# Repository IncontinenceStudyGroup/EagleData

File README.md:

# EagleData

Mits design pro で基板外径などのラインを作成するときは右上の`アプリケーション`ボタンから`Converter`モードにしてからおこなう．

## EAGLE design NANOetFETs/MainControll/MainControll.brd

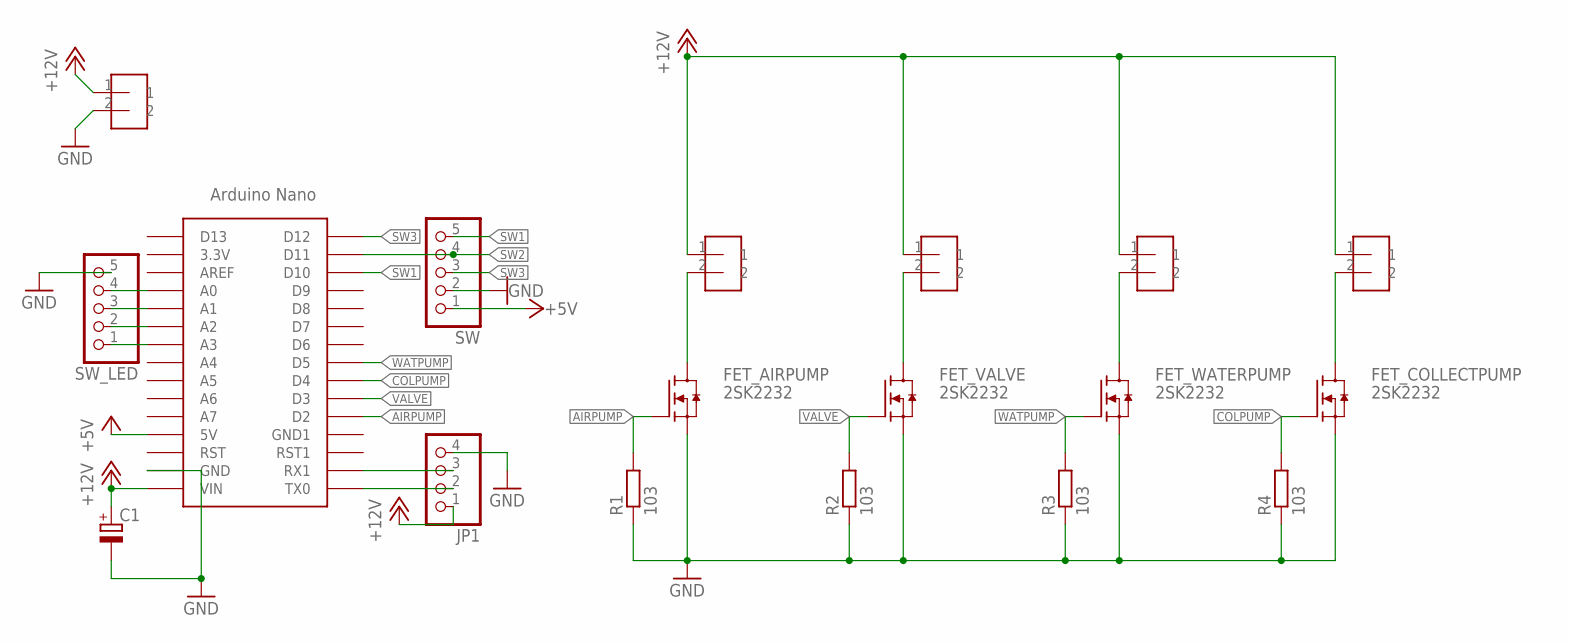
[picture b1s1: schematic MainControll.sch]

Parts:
C1: CPOL-EUE2.5-5; E2,5-5
FET_AIRPUMP: 2SK2232; TO220
FET_COLLECTPUMP: 2SK2232; TO220
FET_VALVE: 2SK2232; TO220
FET_WATERPUMP: 2SK2232; TO220
JP1: PINHD-1X4; 1X04
R1, R2, R3, R4: 103; 0204/5
SW: PINHD-1X5; 1X05
SW_LED: PINHD-1X5; 1X05
TERMINAL_AIRPUMP: TERMINAL_BLOCK_5.08MM; TERMINAL_BLOCK_5.8MM
TERMINAL_COLLECTPUMP: TERMINAL_BLOCK_5.08MM; TERMINAL_BLOCK_5.8MM
TERMINAL_VALVE: TERMINAL_BLOCK_5.08MM; TERMINAL_BLOCK_5.8MM
TERMINAL_WATERPUMP: TERMINAL_BLOCK_5.08MM; TERMINAL_BLOCK_5.8MM
U$1: TERMINAL_BLOCK_5.08MM; TERMINAL_BLOCK_5.8MM
U$2: NANO_DIL_RECEPTOR; NANO_DIL

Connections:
+5V: SW.1, U$2.5V
+12V: C1.+, JP1.1, TERMINAL_AIRPUMP.1, TERMINAL_COLLECTPUMP.1, TERMINAL_VALVE.1, TERMINAL_WATERPUMP.1, U$1.1, U$2.VIN
AIRPUMP: FET_AIRPUMP.1 (G), R1.2, U$2.D2
COLPUMP: FET_COLLECTPUMP.1 (G), R4.2, U$2.D4
GND: C1.-, FET_AIRPUMP.3 (S), FET_COLLECTPUMP.3 (S), FET_VALVE.3 (S), FET_WATERPUMP.3 (S), JP1.4, R1.1, R2.1, R3.1, R4.1, SW.2, SW_LED.5, U$1.2, U$2.GND
unnamed: JP1.3, U$2.RX1
unnamed: JP1.2, U$2.TX0
unnamed: FET_AIRPUMP.2 (D), TERMINAL_AIRPUMP.2
unnamed: FET_VALVE.2 (D), TERMINAL_VALVE.2
unnamed: FET_WATERPUMP.2 (D), TERMINAL_WATERPUMP.2
unnamed: FET_COLLECTPUMP.2 (D), TERMINAL_COLLECTPUMP.2
unnamed: SW_LED.4, U$2.A0
unnamed: SW_LED.3, U$2.A1
unnamed: SW_LED.2, U$2.A2
unnamed: SW_LED.1, U$2.A3
SW1: SW.5, U$2.D10
SW2: SW.4, U$2.D11
SW3: SW.3, U$2.D12
VALVE: FET_VALVE.1 (G), R2.2, U$2.D3
WATPUMP: FET_WATERPUMP.1 (G), R3.2, U$2.D5

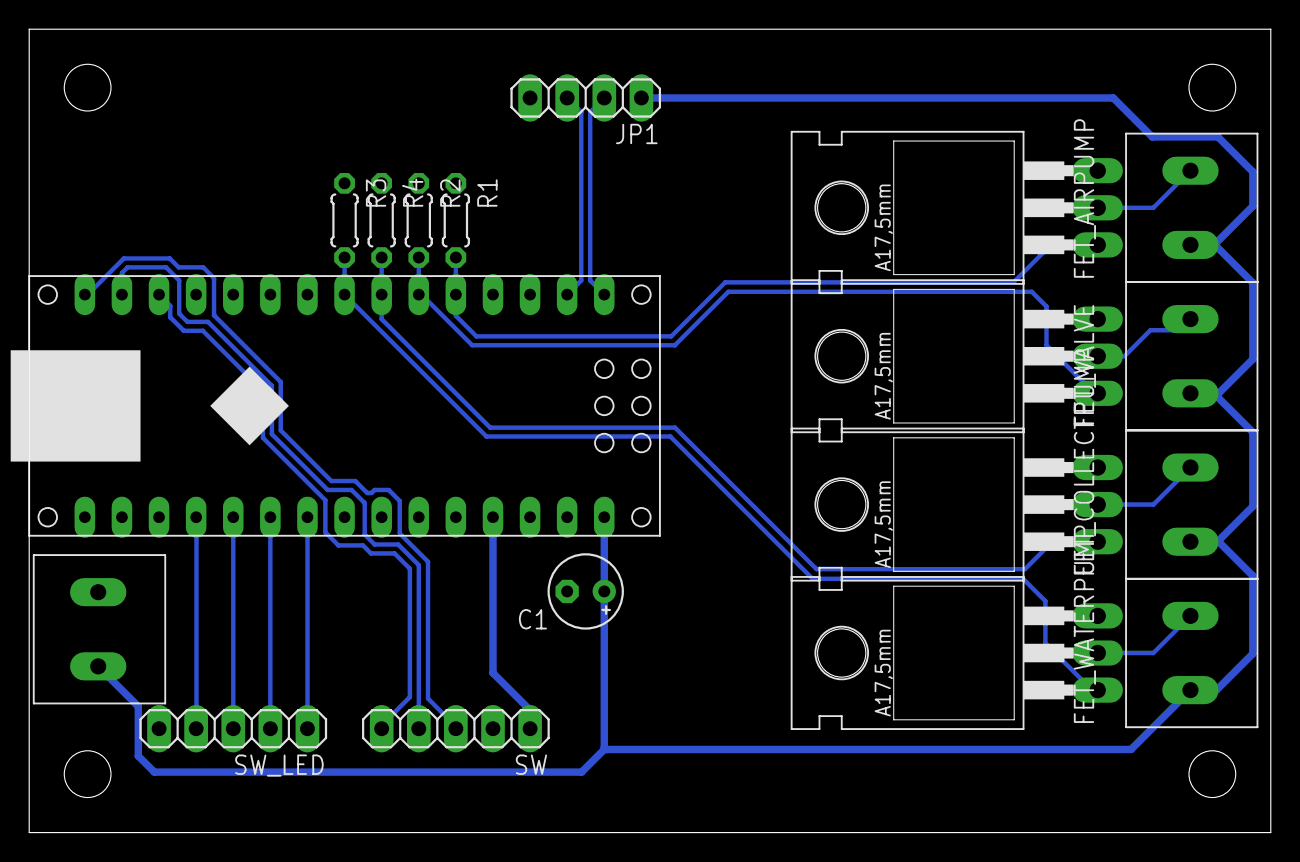
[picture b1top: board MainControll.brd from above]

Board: 2 copper layers, 85.0 x 55.0 mm, 18 parts (0 on the bottom side), 20 nets.

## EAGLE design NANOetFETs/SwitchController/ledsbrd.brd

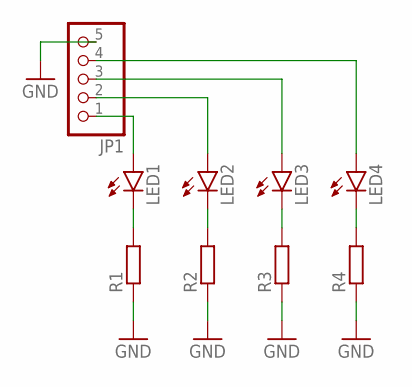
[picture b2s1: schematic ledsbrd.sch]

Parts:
JP1: PINHD-1X5; 1X05
LED1, LED2, LED3, LED4: LED5MM
R1, R2, R3, R4: R-EU_0204/5; 0204/5

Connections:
GND: JP1.5, R1.1, R2.1, R3.1, R4.1
unnamed: LED1.K (C), R1.2
unnamed: LED2.K (C), R2.2
unnamed: LED3.K (C), R3.2
unnamed: LED4.K (C), R4.2
unnamed: JP1.1, LED1.A
unnamed: JP1.2, LED2.A
unnamed: JP1.3, LED3.A
unnamed: JP1.4, LED4.A

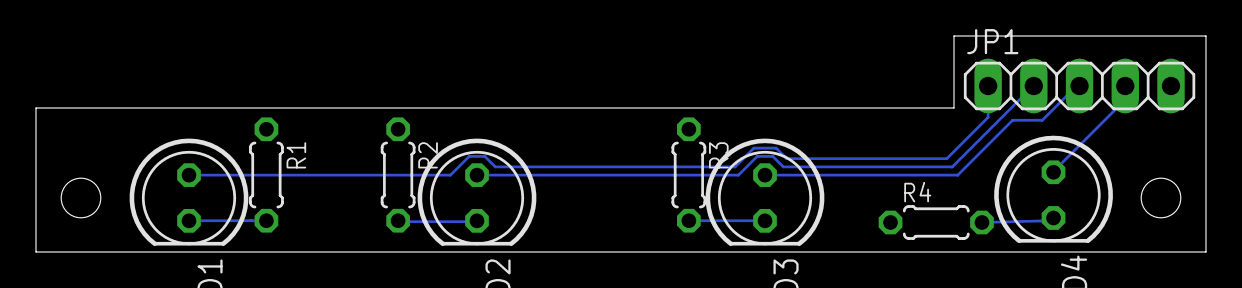
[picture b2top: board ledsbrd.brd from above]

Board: 2 copper layers, 65.0 x 12.0 mm, 9 parts (0 on the bottom side), 9 nets.

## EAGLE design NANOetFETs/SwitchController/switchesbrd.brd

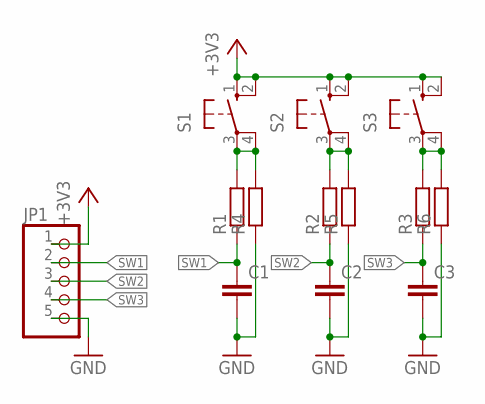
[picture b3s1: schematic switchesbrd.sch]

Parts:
C1, C2, C3: C-EU025-025X050; C025-025X050
JP1: PINHD-1X5; 1X05
R1, R2, R3, R4, R5, R6: R-EU_0204/5; 0204/5
S1, S2, S3: 10-XX; B3F-10XX

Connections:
+3V3: JP1.1, S1.1 (S), S1.2 (S1), S2.1 (S), S2.2 (S1), S3.1 (S), S3.2 (S1)
GND: C1.2, C2.2, C3.2, JP1.5, R4.1, R5.1, R6.1
unnamed: R1.2, R4.2, S1.3, S1.4 (P1)
unnamed: R2.2, R5.2, S2.3, S2.4 (P1)
unnamed: R3.2, R6.2, S3.3, S3.4 (P1)
SW1: C1.1, JP1.2, R1.1
SW2: C2.1, JP1.3, R2.1
SW3: C3.1, JP1.4, R3.1

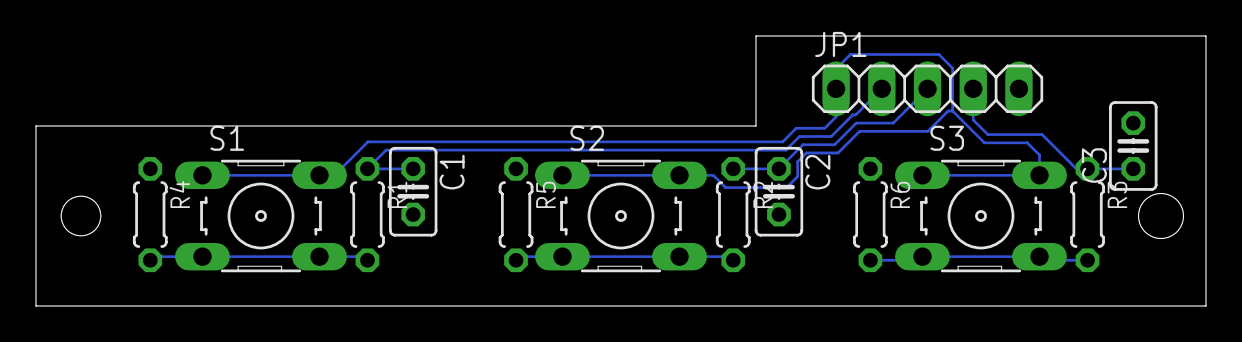
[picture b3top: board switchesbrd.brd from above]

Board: 2 copper layers, 65.0 x 15.0 mm, 13 parts (0 on the bottom side), 8 nets.

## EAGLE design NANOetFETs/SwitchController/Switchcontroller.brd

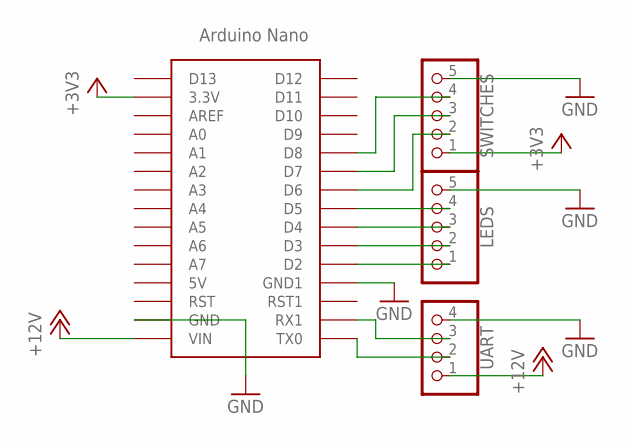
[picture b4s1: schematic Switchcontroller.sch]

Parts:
LEDS: PINHD-1X5; 1X05
SWITCHES: PINHD-1X5; 1X05
U$1: NANO_DIL_RECEPTORPIN-M1; NANO_DIL_M1
UART: PINHD-1X4; 1X04

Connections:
+3V3: SWITCHES.1, U$1.3.3V
+12V: U$1.VIN, UART.1
GND: LEDS.5, SWITCHES.5, U$1.GND, U$1.GND1, UART.4
unnamed: U$1.TX0, UART.2
unnamed: U$1.RX1, UART.3
unnamed: LEDS.3, U$1.D4
unnamed: LEDS.2, U$1.D3
unnamed: LEDS.1, U$1.D2
unnamed: LEDS.4, U$1.D5
unnamed: SWITCHES.2, U$1.D6
unnamed: SWITCHES.3, U$1.D7
unnamed: SWITCHES.4, U$1.D8

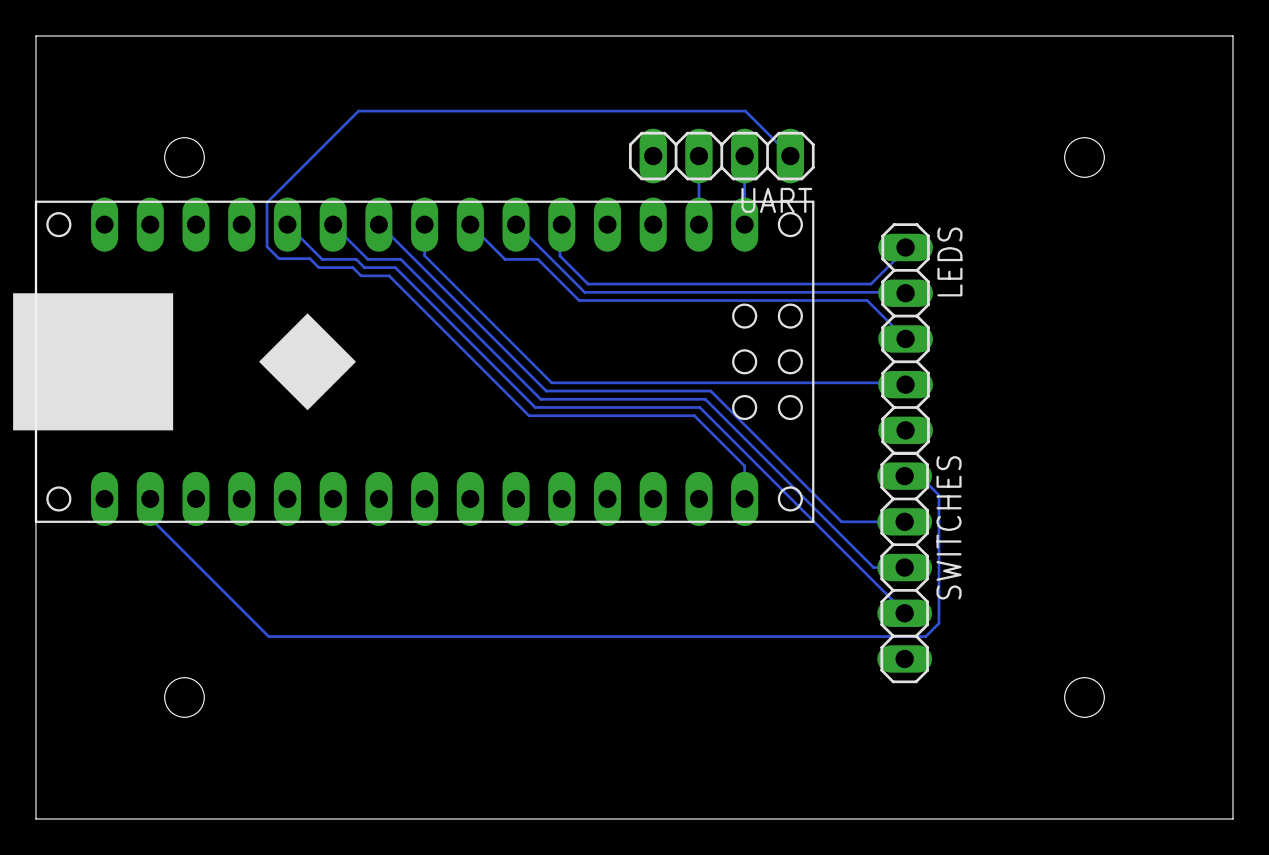
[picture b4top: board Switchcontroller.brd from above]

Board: 2 copper layers, 66.5 x 43.5 mm, 4 parts (0 on the bottom side), 12 nets.

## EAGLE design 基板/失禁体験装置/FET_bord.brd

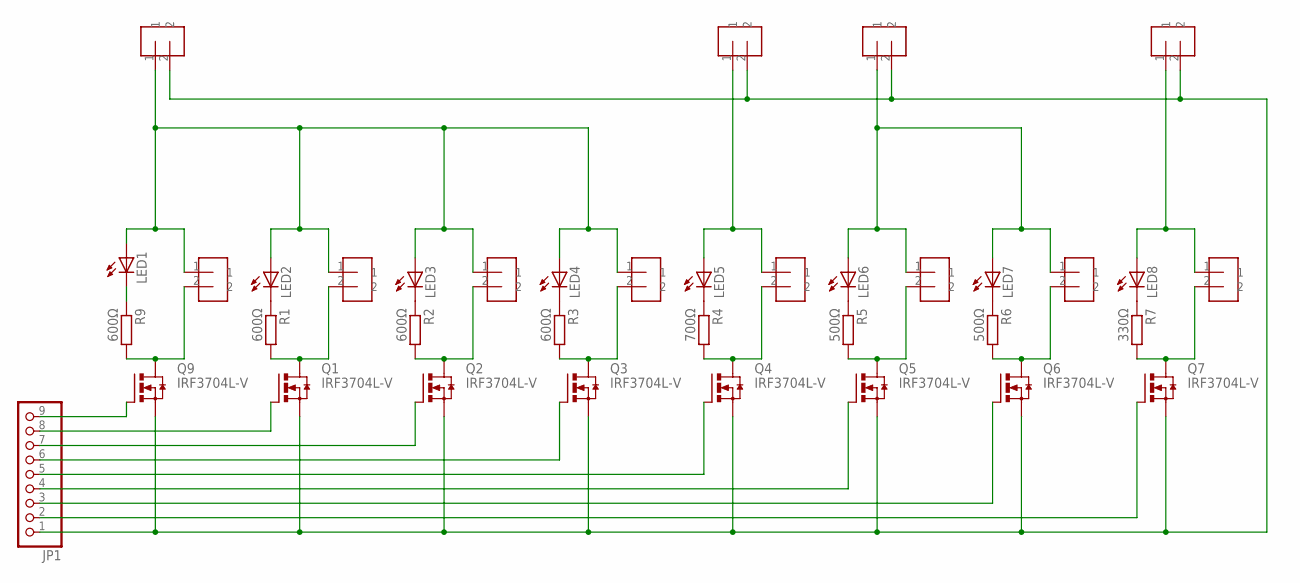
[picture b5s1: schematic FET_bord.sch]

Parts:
3.3V, 5V, 7V, 12V: TERMINAL_BLOCK_5.08MM; TERMINAL_BLOCK_5.8MM
JP1: PINHD-1X9; 1X09
LED1, LED2, LED3, LED4, LED5, LED6, LED7, LED8: LED3MM
Q1, Q2, Q3, Q4, Q5, Q6, Q7, Q9: IRF3704L-V; TO262-V
R1, R2, R3, R9: 600Ω; 0207/15
R4: 700Ω; 0207/15
R5, R6: 500Ω; 0207/15
R7: 330Ω; 0207/15
U$1, U$2, U$3, U$4, U$5, U$6, U$7, U$8: TERMINAL_BLOCK_5.08MM; TERMINAL_BLOCK_5.8MM

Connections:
unnamed: LED2.K (C), R1.1
unnamed: 12V.1, LED1.A, LED2.A, LED3.A, LED4.A, U$1.1, U$2.1, U$3.1, U$4.1
unnamed: Q1.2 (D), R1.2, U$2.2
unnamed: LED3.K (C), R2.1
unnamed: LED4.K (C), R3.1
unnamed: Q2.2 (D), R2.2, U$3.2
unnamed: LED5.K (C), R4.1
unnamed: LED8.K (C), R7.1
unnamed: LED1.K (C), R9.1
unnamed: LED7.K (C), R6.1
unnamed: Q9.2 (D), R9.2, U$1.2
unnamed: Q3.2 (D), R3.2, U$4.2
unnamed: LED6.K (C), R5.1
unnamed: 7V.1, LED5.A, U$5.1
unnamed: Q4.2 (D), R4.2, U$5.2
unnamed: Q5.2 (D), R5.2, U$6.2
unnamed: 5V.1, LED6.A, LED7.A, U$6.1, U$7.1
unnamed: Q6.2 (D), R6.2, U$7.2
unnamed: 3.3V.1, LED8.A, U$8.1
unnamed: Q7.2 (D), R7.2, U$8.2
unnamed: JP1.9, Q9.1 (G)
unnamed: JP1.8, Q1.1 (G)
unnamed: JP1.7, Q2.1 (G)
unnamed: JP1.6, Q3.1 (G)
unnamed: JP1.5, Q4.1 (G)
unnamed: JP1.4, Q5.1 (G)
unnamed: JP1.3, Q6.1 (G)
unnamed: JP1.2, Q7.1 (G)
unnamed: 3.3V.2, 5V.2, 7V.2, 12V.2, JP1.1, Q1.3 (S), Q2.3 (S), Q3.3 (S), Q4.3 (S), Q5.3 (S), Q6.3 (S), Q7.3 (S), Q9.3 (S)

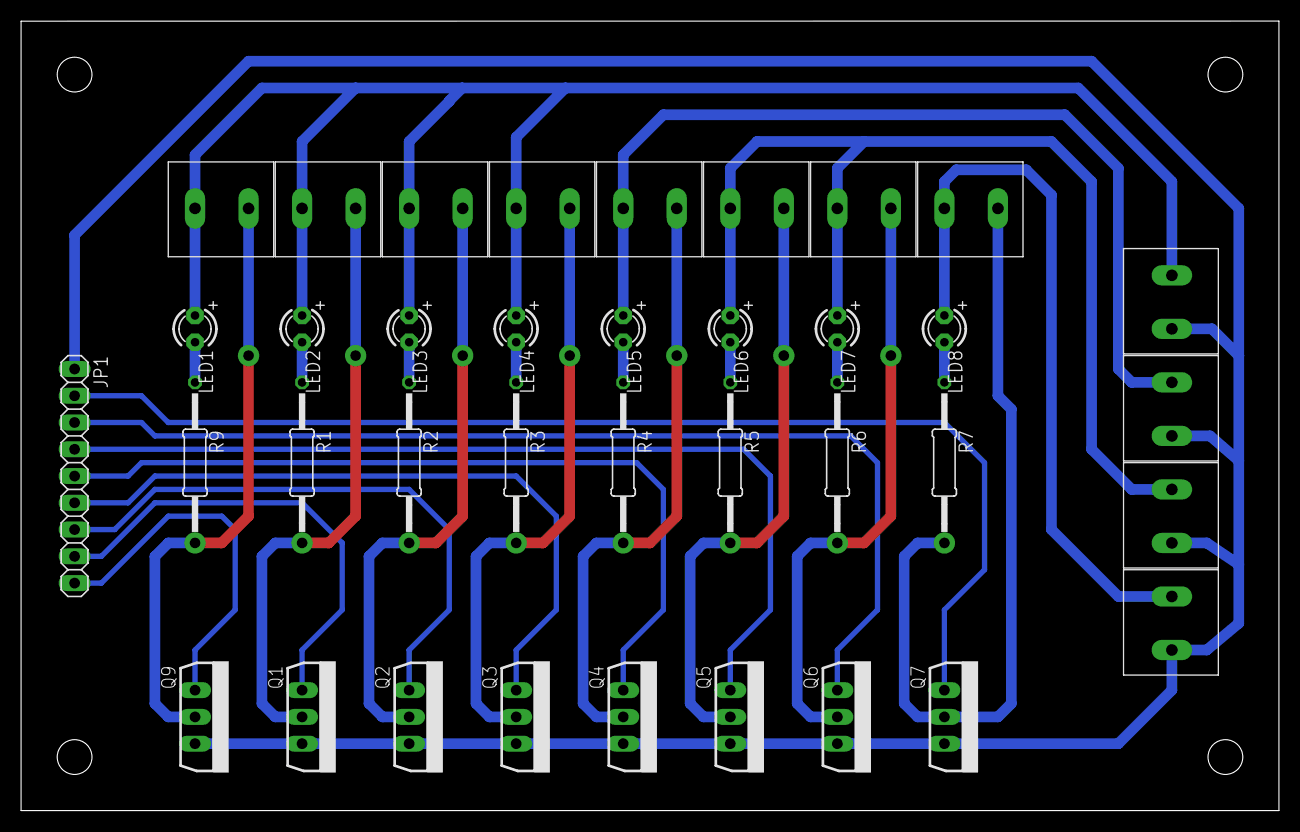
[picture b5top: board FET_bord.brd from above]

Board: 2 copper layers, 119.4 x 74.9 mm, 37 parts (0 on the bottom side), 29 nets.

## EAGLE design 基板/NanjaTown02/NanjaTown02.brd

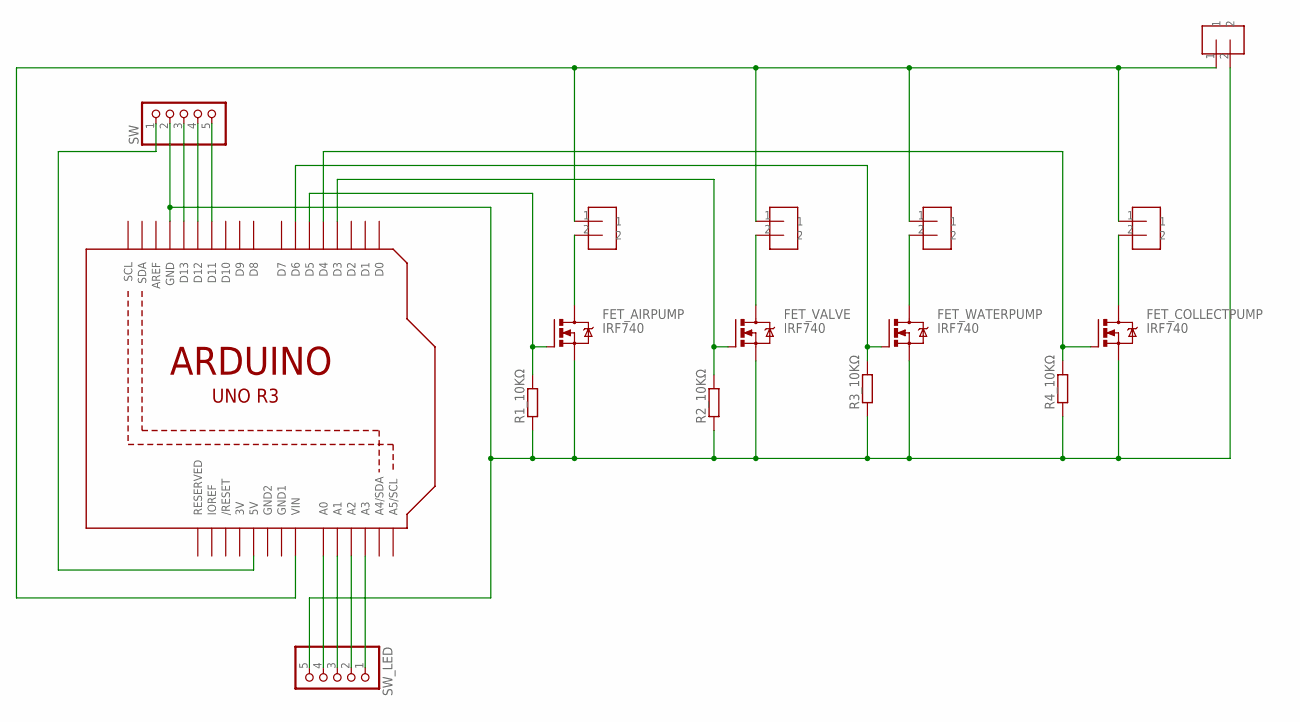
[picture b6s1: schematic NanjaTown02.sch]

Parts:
FET_AIRPUMP: IRF740; TO220BV
FET_COLLECTPUMP: IRF740; TO220BV
FET_VALVE: IRF740; TO220BV
FET_WATERPUMP: IRF740; TO220BV
R1_10KΩ, R2_10KΩ, R3_10KΩ, R4_10KΩ: R-EU_0207/10; 0207/10
SW: PINHD-1X5; 1X05
SW_LED: PINHD-1X5/90; 1X05/90
TERMINAL_AIRPUMP: TERMINAL_BLOCK_5.08MM; TERMINAL_BLOCK_5.8MM
TERMINAL_COLLECTPUMP: TERMINAL_BLOCK_5.08MM; TERMINAL_BLOCK_5.8MM
TERMINAL_VALVE: TERMINAL_BLOCK_5.08MM; TERMINAL_BLOCK_5.8MM
TERMINAL_WATERPUMP: TERMINAL_BLOCK_5.08MM; TERMINAL_BLOCK_5.8MM
U1: ARDUINOR3-DIMENSION; ARDUINOR3
U$1: TERMINAL_BLOCK_5.08MM; TERMINAL_BLOCK_5.8MM

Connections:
3V: U1.3V
GND1: U1.GND1
GND2: U1.GND2
unnamed: FET_AIRPUMP.G, R1_10KΩ.2, U1.D5
unnamed: FET_VALVE.G, R2_10KΩ.2, U1.D3
unnamed: FET_WATERPUMP.G, R3_10KΩ.2, U1.D6
unnamed: FET_COLLECTPUMP.G, R4_10KΩ.2, U1.D4
unnamed: TERMINAL_AIRPUMP.1, TERMINAL_COLLECTPUMP.1, TERMINAL_VALVE.1, TERMINAL_WATERPUMP.1, U1.VIN, U$1.1
unnamed: FET_AIRPUMP.D, TERMINAL_AIRPUMP.2
unnamed: FET_VALVE.D, TERMINAL_VALVE.2
unnamed: FET_WATERPUMP.D, TERMINAL_WATERPUMP.2
unnamed: FET_COLLECTPUMP.D, TERMINAL_COLLECTPUMP.2
unnamed: SW_LED.4, U1.A0
unnamed: SW_LED.3, U1.A1
unnamed: SW_LED.2, U1.A2
unnamed: SW_LED.1, U1.A3
unnamed: FET_AIRPUMP.S, FET_COLLECTPUMP.S, FET_VALVE.S, FET_WATERPUMP.S, R1_10KΩ.1, R2_10KΩ.1, R3_10KΩ.1, R4_10KΩ.1, SW.2, SW_LED.5, U1.GND, U$1.2
unnamed: SW.5, U1.D11
unnamed: SW.4, U1.D12
unnamed: SW.3, U1.D13
unnamed: SW.1, U1.5V

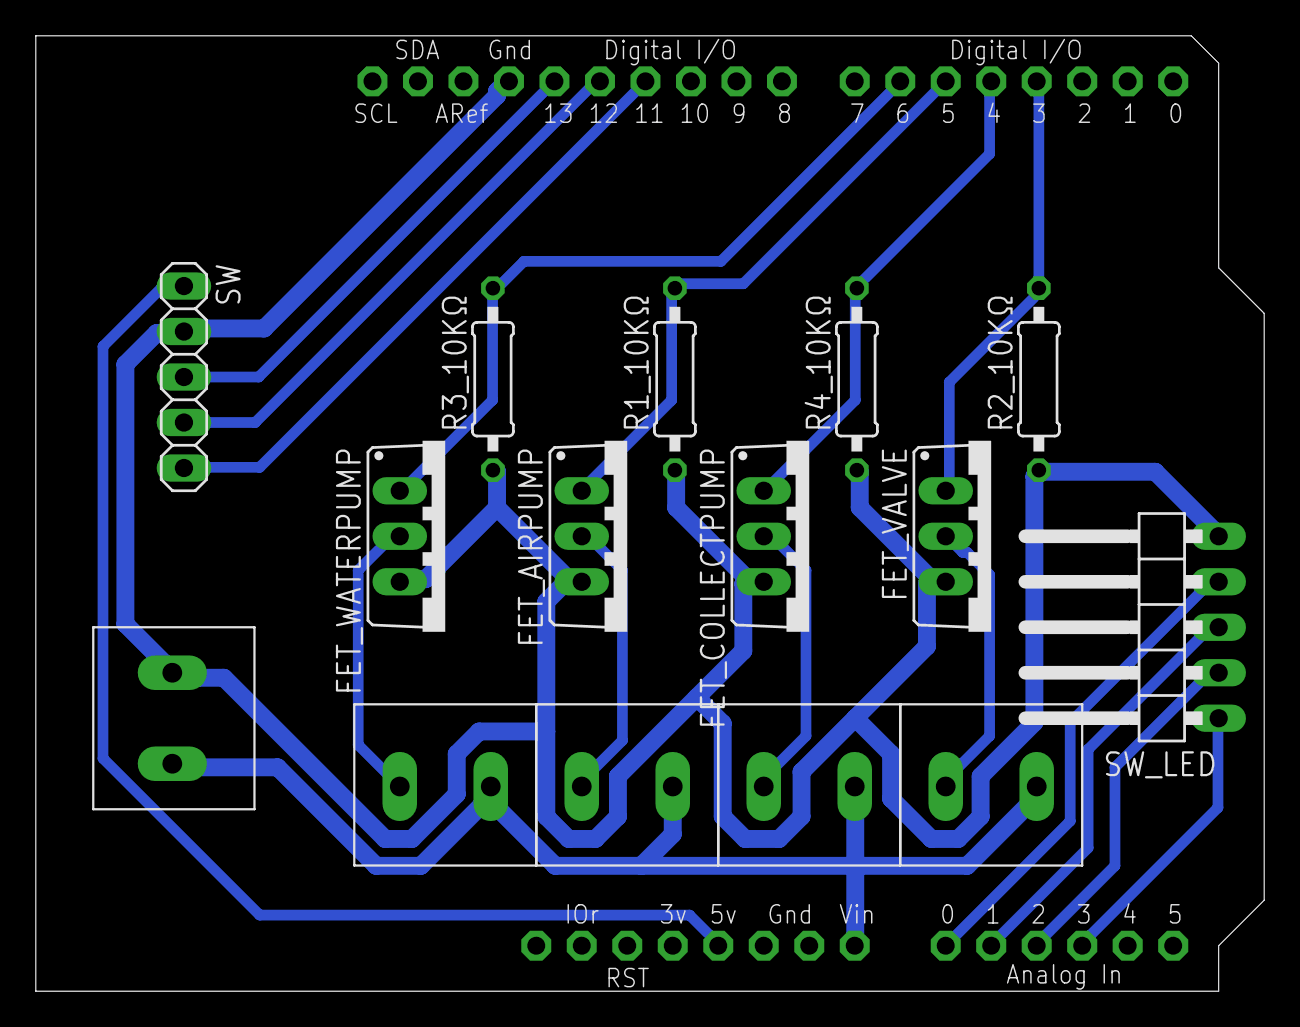
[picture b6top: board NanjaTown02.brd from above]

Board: 2 copper layers, 68.6 x 53.3 mm, 16 parts (0 on the bottom side), 18 nets.

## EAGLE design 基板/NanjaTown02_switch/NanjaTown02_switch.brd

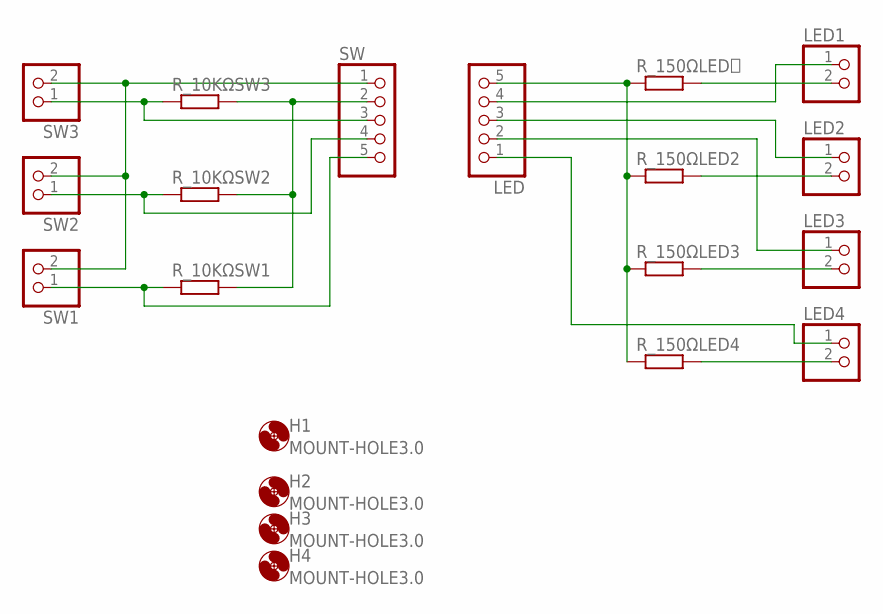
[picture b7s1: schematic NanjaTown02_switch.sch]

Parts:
H1, H2, H3, H4: MOUNT-HOLE3.0; 3,0
LED: PINHD-1X5; 1X05
LED1, LED2, LED3, LED4: PINHD-1X2; 1X02
R_10KΩSW1, R_10KΩSW2, R_10KΩSW3, R_150ΩLED2, R_150ΩLED3, R_150ΩLED4, R_150ΩLED１: R-EU_0207/10; 0207/10
SW: PINHD-1X5; 1X05
SW1, SW2, SW3: PINHD-1X2; 1X02

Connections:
unnamed: SW.1, SW1.2, SW2.2, SW3.2
unnamed: R_10KΩSW3.1, SW.3, SW3.1
unnamed: R_10KΩSW2.1, SW.4, SW2.1
unnamed: R_10KΩSW1.1, SW.5, SW1.1
unnamed: R_10KΩSW1.2, R_10KΩSW2.2, R_10KΩSW3.2, SW.2
unnamed: LED.5, R_150ΩLED2.1, R_150ΩLED3.1, R_150ΩLED4.1, R_150ΩLED１.1
unnamed: LED1.2, R_150ΩLED１.2
unnamed: LED2.2, R_150ΩLED2.2
unnamed: LED3.2, R_150ΩLED3.2
unnamed: LED4.2, R_150ΩLED4.2
unnamed: LED.4, LED1.1
unnamed: LED.3, LED2.1
unnamed: LED.2, LED3.1
unnamed: LED.1, LED4.1

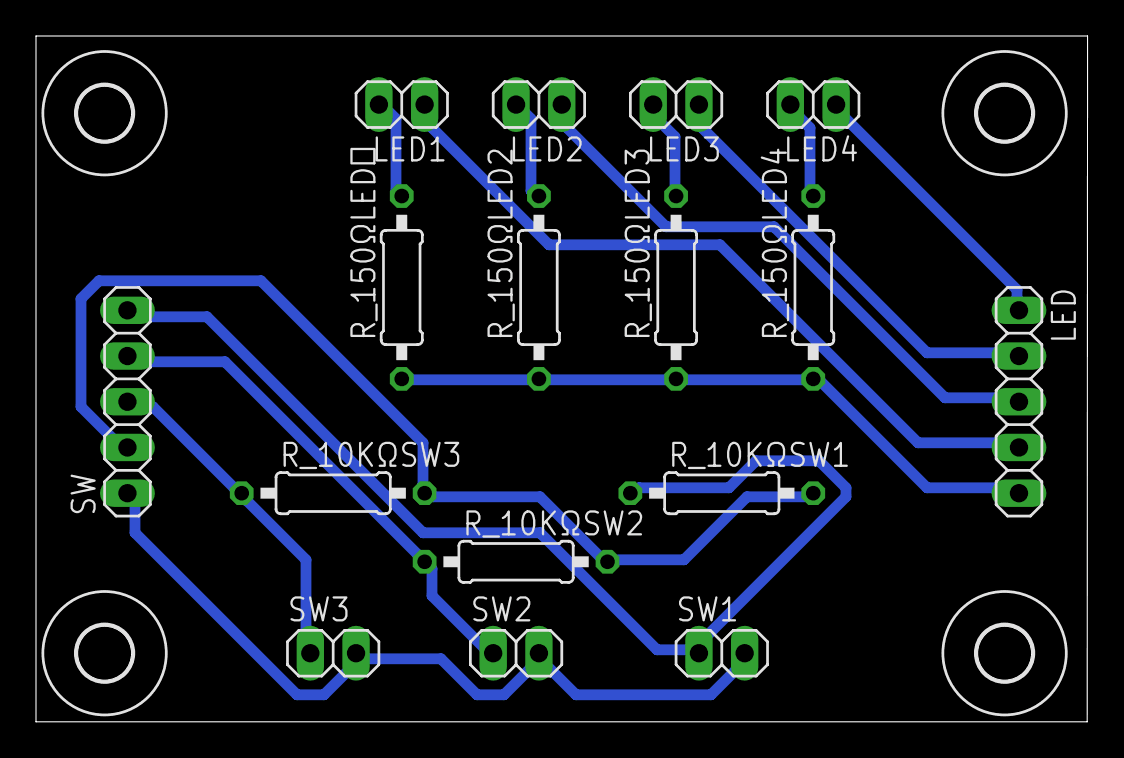
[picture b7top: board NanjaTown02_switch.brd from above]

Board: 2 copper layers, 58.4 x 38.1 mm, 20 parts (0 on the bottom side), 14 nets.

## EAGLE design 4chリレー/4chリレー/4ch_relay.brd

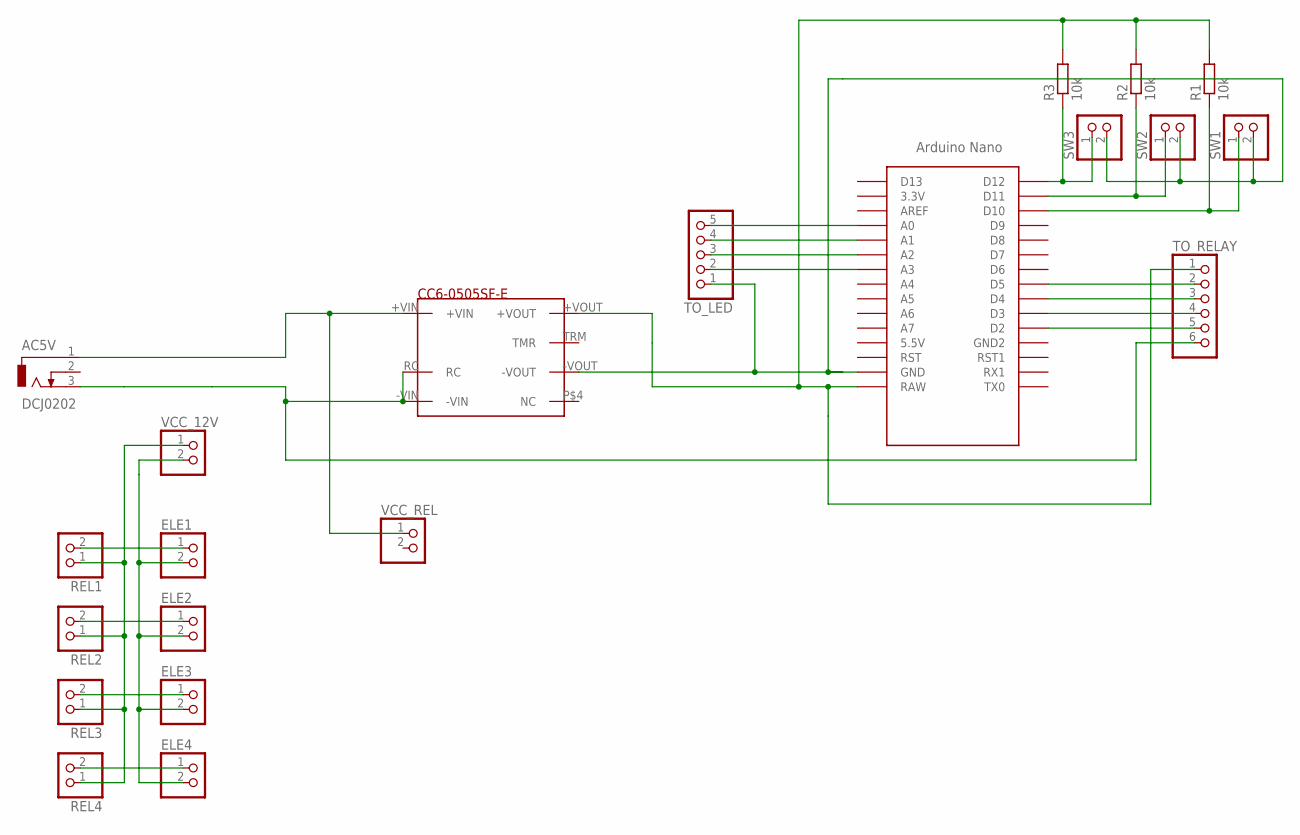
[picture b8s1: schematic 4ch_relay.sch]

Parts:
AC5V: DCJ0202
DC-DC1: DC-DC-CONVERTER; DC_DC_CONVERTER
ELE1, ELE2, ELE3, ELE4: PINHD-1X2; 1X02
R1, R2, R3: 10k; 0207/10
REL1, REL2, REL3, REL4: PINHD-1X2; 1X02
SW1, SW2, SW3: PINHD-1X2; 1X02
TO_LED: PINHD-1X5; 1X05
TO_RELAY: PINHD-1X6; 1X06
U$1: NANO
VCC_12V: PINHD-1X2; 1X02
VCC_REL: PINHD-1X2; 1X02

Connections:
unnamed: TO_LED.5, U$1.A0
unnamed: AC5V.1, DC-DC1.+VIN, VCC_REL.1
unnamed: TO_LED.4, U$1.A1
unnamed: TO_LED.3, U$1.A2
unnamed: TO_LED.2, U$1.A3
unnamed: R3.1, SW3.1, U$1.D12
unnamed: R2.1, SW2.1, U$1.D11
unnamed: R1.1, SW1.1, U$1.D10
unnamed: TO_RELAY.2, U$1.D5
unnamed: TO_RELAY.3, U$1.D4
unnamed: TO_RELAY.4, U$1.D3
unnamed: TO_RELAY.5, U$1.D2
unnamed: DC-DC1.+VOUT, R1.2, R2.2, R3.2, TO_RELAY.1, U$1.RAW
unnamed: DC-DC1.-VOUT, SW1.2, SW2.2, SW3.2, TO_LED.1, U$1.GND
unnamed: ELE1.1, REL1.2
unnamed: ELE2.1, REL2.2
unnamed: ELE3.1, REL3.2
unnamed: ELE4.1, REL4.2
unnamed: REL1.1, REL2.1, REL3.1, REL4.1, VCC_12V.1
unnamed: ELE1.2, ELE2.2, ELE3.2, ELE4.2, VCC_12V.2
unnamed: AC5V.3, DC-DC1.-VIN, DC-DC1.RC, TO_RELAY.6

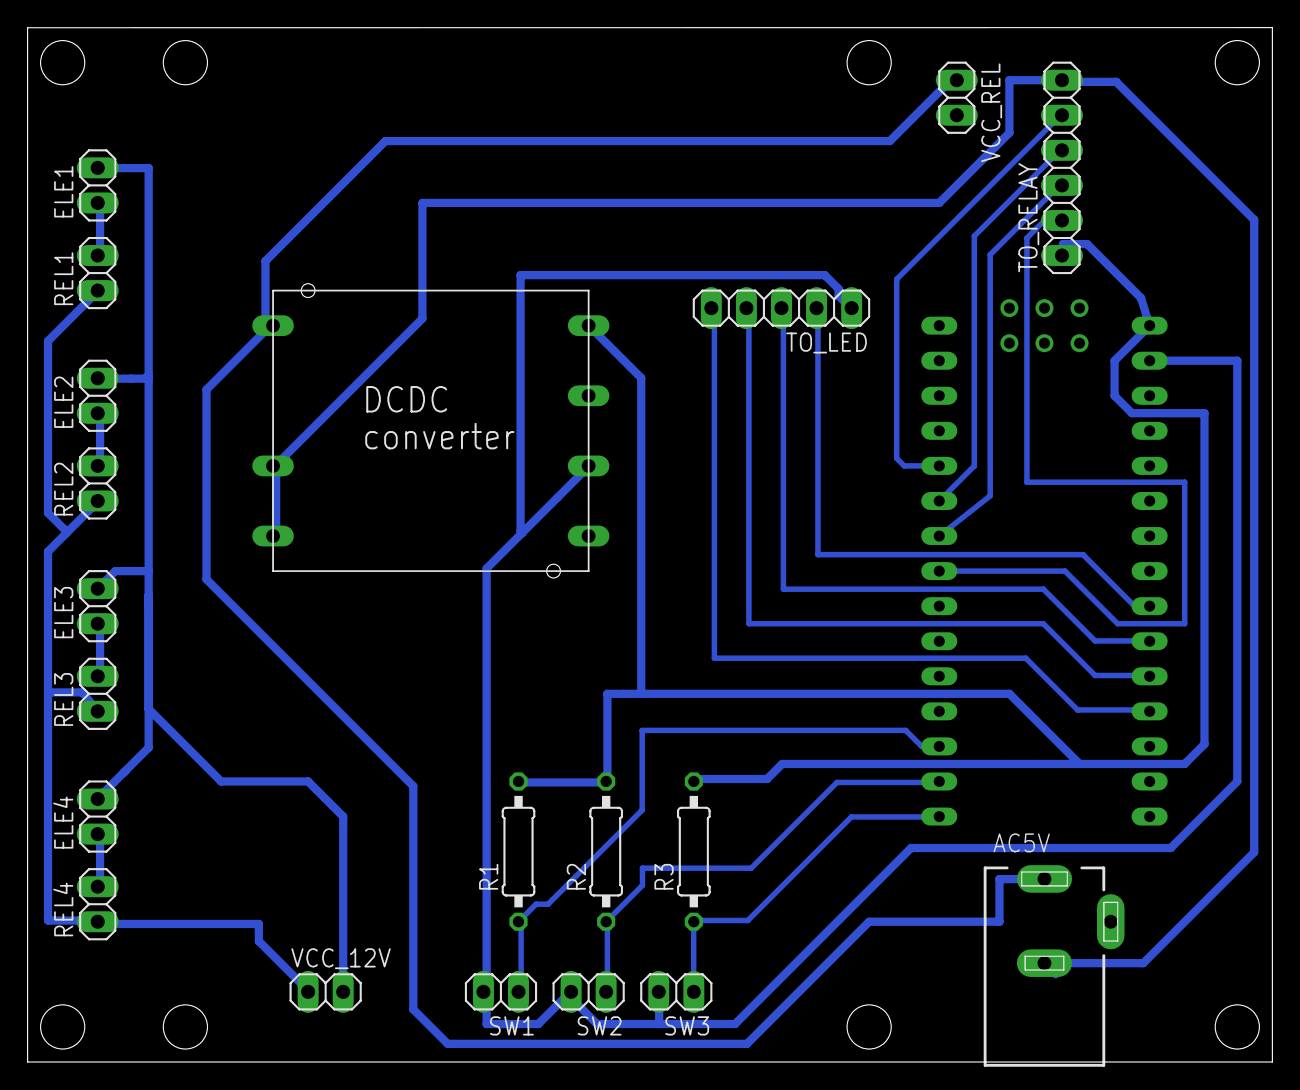
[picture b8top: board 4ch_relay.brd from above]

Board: 2 copper layers, 90.2 x 74.9 mm, 21 parts (0 on the bottom side), 21 nets.

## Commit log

2019-07-31 add files
2019-07-31 added new folder that includes Nano-FET ver.
2019-08-27 1st prototype
2019-08-27 added controller's circuits
2021-12-14 Re-routed some signals to fix errors of clearance; Added Gerber files and a Mit file; Added git-ignore setting file
2022-01-16 brd手直し
2022-01-16 シルク追加
2022-01-17 release
2022-03-22 Modifed wire thinkness bolder; Rerouted as well;
